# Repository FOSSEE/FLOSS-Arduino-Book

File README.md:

# FLOSS-Arduino-Book
[Scilab](https://www.scilab.org/), [Xcos](https://www.scilab.org/software/xcos), [Python](https://www.python.org/), [Julia](https://julialang.org/), and [OpenModelica](https://www.openmodelica.org/) are powerful and free. However, there has not been much literature that teaches how to use them to program the versatile [Arduino Uno](https://www.arduino.cc/en/Guide/ArduinoUno). To address this gap, we have written this series of books. We have provided code written in all of these open-source software. The reader is recommended to go through the book that covers a particular software. For the sake of convenience, we call each of the tools (**Scilab**, **Xcos**, **Python**, **Julia**, and **OpenModelica**) as **FLOSS** in these books. To know more about **FLOSS**, one may want to visit [FOSSEE](https://fossee.in/). 

The books are as given below:
* [Microcontroller programming with Arduino, Scilab, and Xcos](https://github.com/FOSSEE/FLOSS-Arduino-Book/blob/master/scilab.pdf)
* [Microcontroller programming with Arduino and Julia](https://github.com/FOSSEE/FLOSS-Arduino-Book/blob/master/julia.pdf)
* [Microcontroller programming with Arduino and OpenModelica](https://github.com/FOSSEE/FLOSS-Arduino-Book/blob/master/openmodelica.pdf)
* [Microcontroller programming with Arduino and Python](https://github.com/FOSSEE/FLOSS-Arduino-Book/blob/master/python.pdf)

The consolidated book (which covers all the four FLOSSs mentioned above) is available at [FLOSS-Arduino](https://github.com/FOSSEE/FLOSS-Arduino-Book/blob/master/floss-arduino.pdf), and the code mentioned in the book are available at [Origin](https://github.com/FOSSEE/FLOSS-Arduino-Book/tree/master/Origin). 

## Source files to compile the book 
The books have been prepared using [LaTeX](https://www.latex-project.org/). The main LaTeX file is available [here](https://github.com/FOSSEE/FLOSS-Arduino-Book/blob/master/floss-arduino.tex). While compiling, one needs to modify the two paths (`Home` and `Origin`), as mentioned at the top of this file. 

## Reporting an issue 
Any issues faced while executing the code for running the experiments can be reported by opening a `New issue` in the repository. However, the readers are recommended to glance at the existing issues to check whether their issues have already been reported/addressed. One may also write to `FLOSS-arduino@fossee.in` for any queries.

## License 
The soft-copy/electronic-version of these books is released under Creative Commons Attribution-NonCommercial-NoDerivatives (CC BY-NC-ND)
license.  Those who want to use this book for commercial purposes may contact Prof. Kannan Moudgalya.

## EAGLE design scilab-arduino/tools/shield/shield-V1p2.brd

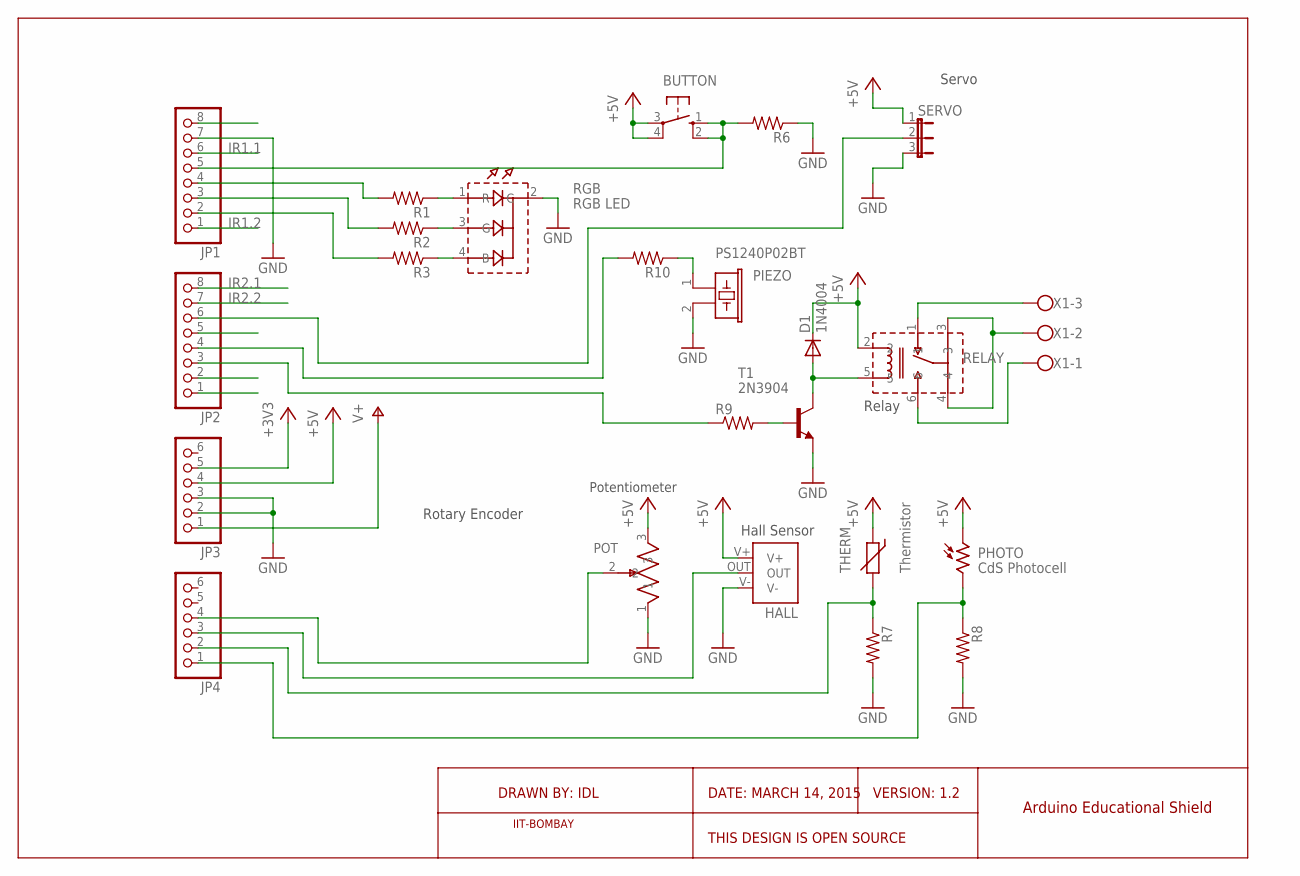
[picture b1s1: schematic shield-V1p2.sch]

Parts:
BUTTON: 10-XX; B3F-10XX
D1: 1N4004; DO41-10
HALL: SS49E; TO_92_SHORT
JP1, JP2: PINHD-1X8; 1X08
JP3, JP4: PINHD-1X6; 1X06
PHOTO: CdS Photocell; TO46-VT200
PIEZO: PS1240P02BT
POT: EVU_POTENTIOMETER; VERT_POT
R1, R2, R3, R6, R7, R8, R9, R10: R-US_0207/10; 0207/10
RELAY: TSC_1FORMC; TSC_RELAY
RGB: RGB LED; RGB_VERTICAL
SERVO: JP2E; JP2
T1: 2N3904; TO92
THERM: Thermistor; R-5
X1: W237-103

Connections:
+3V3: JP3.5
+5V: BUTTON.3, BUTTON.4 (P1), D1.C, HALL.V+, JP3.4, PHOTO.1, POT.3, RELAY.2, SERVO.1, THERM.1
BLUE: JP1.3, R2.2
BUTTON: BUTTON.1 (S), BUTTON.2 (S1), JP1.5, R6.2
GND: HALL.V-, JP1.7, JP3.2, JP3.3, PIEZO.2, POT.1, R6.1, R7.2, R8.2, RGB.2 (C), SERVO.3, T1.3 (E)
GREEN: JP1.2, R3.2
HALL_SENSOR: HALL.OUT, JP4.3
IR1.1: JP1.6
IR1.2: JP1.1
IR2.1: JP2.8
IR2.2: JP2.7
unnamed: R1.1, RGB.1 (R)
unnamed: R2.1, RGB.3 (G)
unnamed: R3.1, RGB.4 (B)
unnamed: PIEZO.1, R10.1
unnamed: D1.A, RELAY.5, T1.1 (C)
unnamed: RELAY.1, X1.3
unnamed: RELAY.3, RELAY.4, X1.2
unnamed: RELAY.6, X1.1
unnamed: R9.2, T1.2 (B)
PHOTOCELL: JP4.1, PHOTO.2, R8.1
PIEZO: JP2.4, R10.2
POTENTIOMETER: JP4.4, POT.2
RED: JP1.4, R1.2
RELAY: JP2.3, R9.1
SERVO: JP2.6, SERVO.2
THERMISTOR: JP4.2, R7.1, THERM.2
UNUSED3: JP2.5
UNUSED4: JP2.2
UNUSED5: JP2.1
V+: JP3.1

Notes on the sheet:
Hall Sensor
Rotary Encoder
Servo
Relay
DRAWN BY: IDL
DATE: MARCH 14, 2015
VERSION: 1.2
THIS DESIGN IS OPEN SOURCE
Arduino Educational Shield
IIT-BOMBAY
Potentiometer

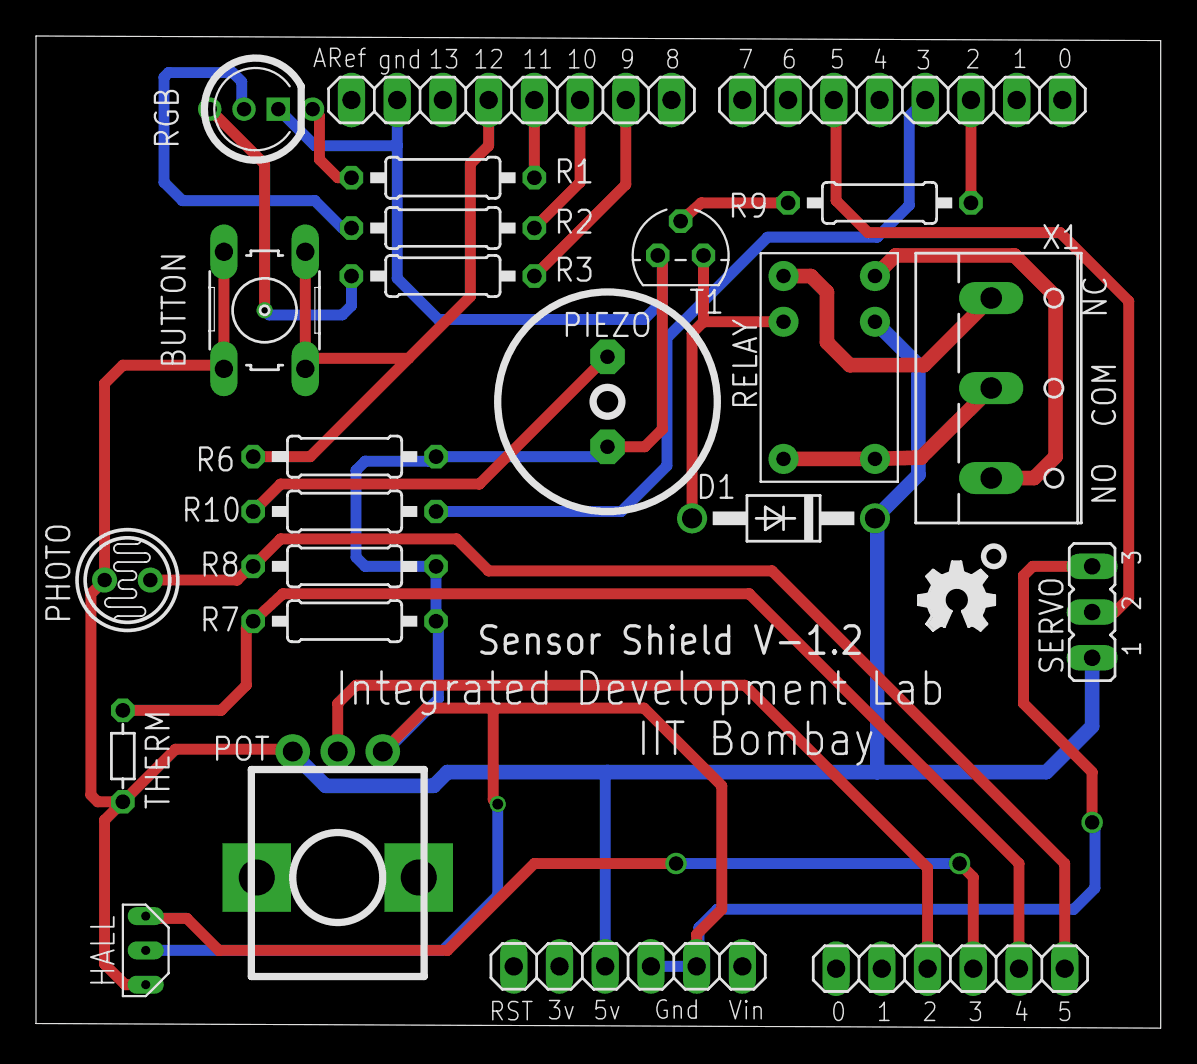
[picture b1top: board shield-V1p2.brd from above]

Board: 2 copper layers, 62.5 x 55.1 mm, 25 parts (0 on the bottom side), 22 nets.

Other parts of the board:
U$1: OSHW_FILLX150_NOTEXT

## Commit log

2021-03-07 Add initial files
2021-03-07 Remove duplicate pdfs
2021-03-09 Reorganised the sections in a big way
2021-03-12 Created the List of Scilab Code Page
2021-03-17 Add breadboard connection for RGB LED
2021-03-17 Add breadboard connection for pushbutton
2021-03-17 Add remaining breadboard connections
2021-03-19 \comment{} has been added now
2021-03-26 Fix spelling issues
2021-03-31 Address the comments of NR
2021-04-01 Add Rajesh Sir's changes
2021-04-03 Add OpenModelica info
2021-04-03 Add OM views
2021-04-04 Add OM files
2021-04-05 Add RGB LED breadboard
2021-04-05 Add OM simulate
2021-04-08 Add breadboard connection for RGB
2021-04-08 Add pushbutton breadboard
2021-04-08 Update switch
2021-04-08 Add pot
2021-04-08 Add breadboard diagrams
2021-04-11 Modify diagrams
2021-04-12 Add Julia installation
2021-04-12 Fix typo
2021-04-15 Update images
2021-04-16 Add image for OMEdit
2021-04-16 Add SerialPorts in Julia
2021-04-22 Add Python on Windows
2021-04-22 Include NM's suggestions
2021-04-22 Add Julia on Windows
2021-04-23 Update Julia download image
2021-04-25 Add OM on windows
2021-04-26 Update the code
2021-04-27 Add NM suggestions
2021-04-27 Update Python toolbox
2021-04-27 Add NM comments
2021-04-29 Update chapter 4
2021-04-29 Add new shield image and fix OM code
2021-04-29 Address NM comments
2021-04-29 Update Xcos com2 images
2021-04-30 Update Arduino instructions
2021-05-01 Update chapter 5
2021-05-01 Add arduino meter and OM files
2021-05-01 Update LDR
2021-05-01 Add OM for LDR
2021-05-01 Remove duplicate image
2021-05-01 Update chapter on LDR
2021-05-02 Add potentiometer updated
2021-05-02 Add Xcos image
2021-05-02 Maintain consistency in LED codes
2021-05-02 Update Arduino OM for LED
2021-05-03 Maintain consistency in pushbutton
2021-05-03 Add thermistor update
2021-05-03 Update codes
2021-05-03 Maintain consistency in LDR codes
2021-05-03 Maintain consistency in pot codes
2021-05-03 Maintain consistency in thermistor codes
2021-05-03 Maintain consistency in servo motor codes
2021-05-03 Maintain consistency in DC motor code
2021-05-04 Fix code files
2021-05-05 Fix chapter on DC motor
2021-05-05 Add Xcos images with com2
2021-05-06 Modify the images in DC motor
2021-05-06 Add servo motor images
2021-05-06 Update pwm image
2021-05-06 Maintain consistency in servo chapter
2021-05-06 Fix OM paths
2021-05-07 update Modbus chapter
2021-05-07 Fix typos
2021-05-07 Add updated shield
2021-05-08 Add threshold issues in thermistor chapter
2021-05-08 Add Modbus points
2021-05-17 Chapters divided software-wise. Main file modified to produce a book with all software or any of the four software: Scilab, Python, Julia and OM, with Arduino IDE coming with every one of these four.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
2021-05-19 Fix chapter 3 for Scilab
2021-05-22 Segment Modbus chapter
2021-05-22 Using the \ifx command, list of code has been made to come correctly
2021-05-22 No change from the previous
2021-05-22 Create scilab book
2021-05-23 Fix warnings due to multiple labels
2021-05-23 I have modified the introduction
2021-05-23 Check introduction for individual books
2021-05-25 Update Julia book
2021-05-25 Update Python book
2021-05-25 Update Scilab and OM book
2021-05-25 Update FLOSS firmware
2021-05-26 Update Modbus flowcharts
2021-06-05 Update OM files
2021-06-06 Modify the names of the books
2021-06-09 Update OM files in the book
2021-06-09 Add reame
2021-06-09 Add Origin folder
2021-06-09 Remove Origin
2021-06-09 Add origin
2021-06-20 Book Titles included, Author lists modified, License information included
2021-06-21 Symbolic link, and files in other directories replaced
2021-06-21 Remove the files having long names
2021-06-21 Update name
2021-06-25 Change the license to ccbyncnd
2021-06-26 Update shield seller info
2021-06-28 Chandrashekhar Dhulipala included as an author in the Julia book
2021-06-29 Rewrote the Appendix
2021-07-01 Email address changed in the appendix
2021-07-05 Vendor information removed
2021-07-05 Recompile to remove funny characters
2022-01-08 Add e-commerce details for the shield
2022-09-17 Modify Appendix needed for publishing hard copy
2022-09-17 Generate the individual book after modifying appendix
2022-10-16 Remove the date of available latest release
2022-11-13 Include Preface in the books
2023-02-08 Replace breadboard images with dark color wires
2023-02-08 Rename the file
2023-02-08 Revert the file name
2023-05-21 Change Home and Origin
2023-07-14 Update procuring hardware information
2023-07-14 Regenerate the books
2023-07-15 Fix the inconsistencies of Uno and UNO by using Uno in all the places
2023-08-26 Fix normal typos
2023-08-26 Generate individual books
2023-08-27 Compile individual books for correct references
2023-09-03 Fix the typos in servo chapter
2023-09-18 Reduce text area
2023-09-19 Recompile for proper citations
2023-11-17 Fix the images and tables going beyond text margins
2024-07-10 add Jupyter notebook
2024-07-10 add file
2024-07-10 Rename prediction of patient health model.ipynb to Health prediction model.ipynb
2024-07-10 update file
2024-07-15 update folder
2024-08-13 Rename Task_ready.ipynb to Weather_prediction_model.ipynb
2024-08-13 Rename model.ipynb to Health_Prediction_model.ipynb
2024-08-13 Rename notebook_file.ipynb to Indian_sign_language_model.ipynb
2025-06-06 Add ElectroBlocks Python examples for Servo, RGB LED, and LED Blink
